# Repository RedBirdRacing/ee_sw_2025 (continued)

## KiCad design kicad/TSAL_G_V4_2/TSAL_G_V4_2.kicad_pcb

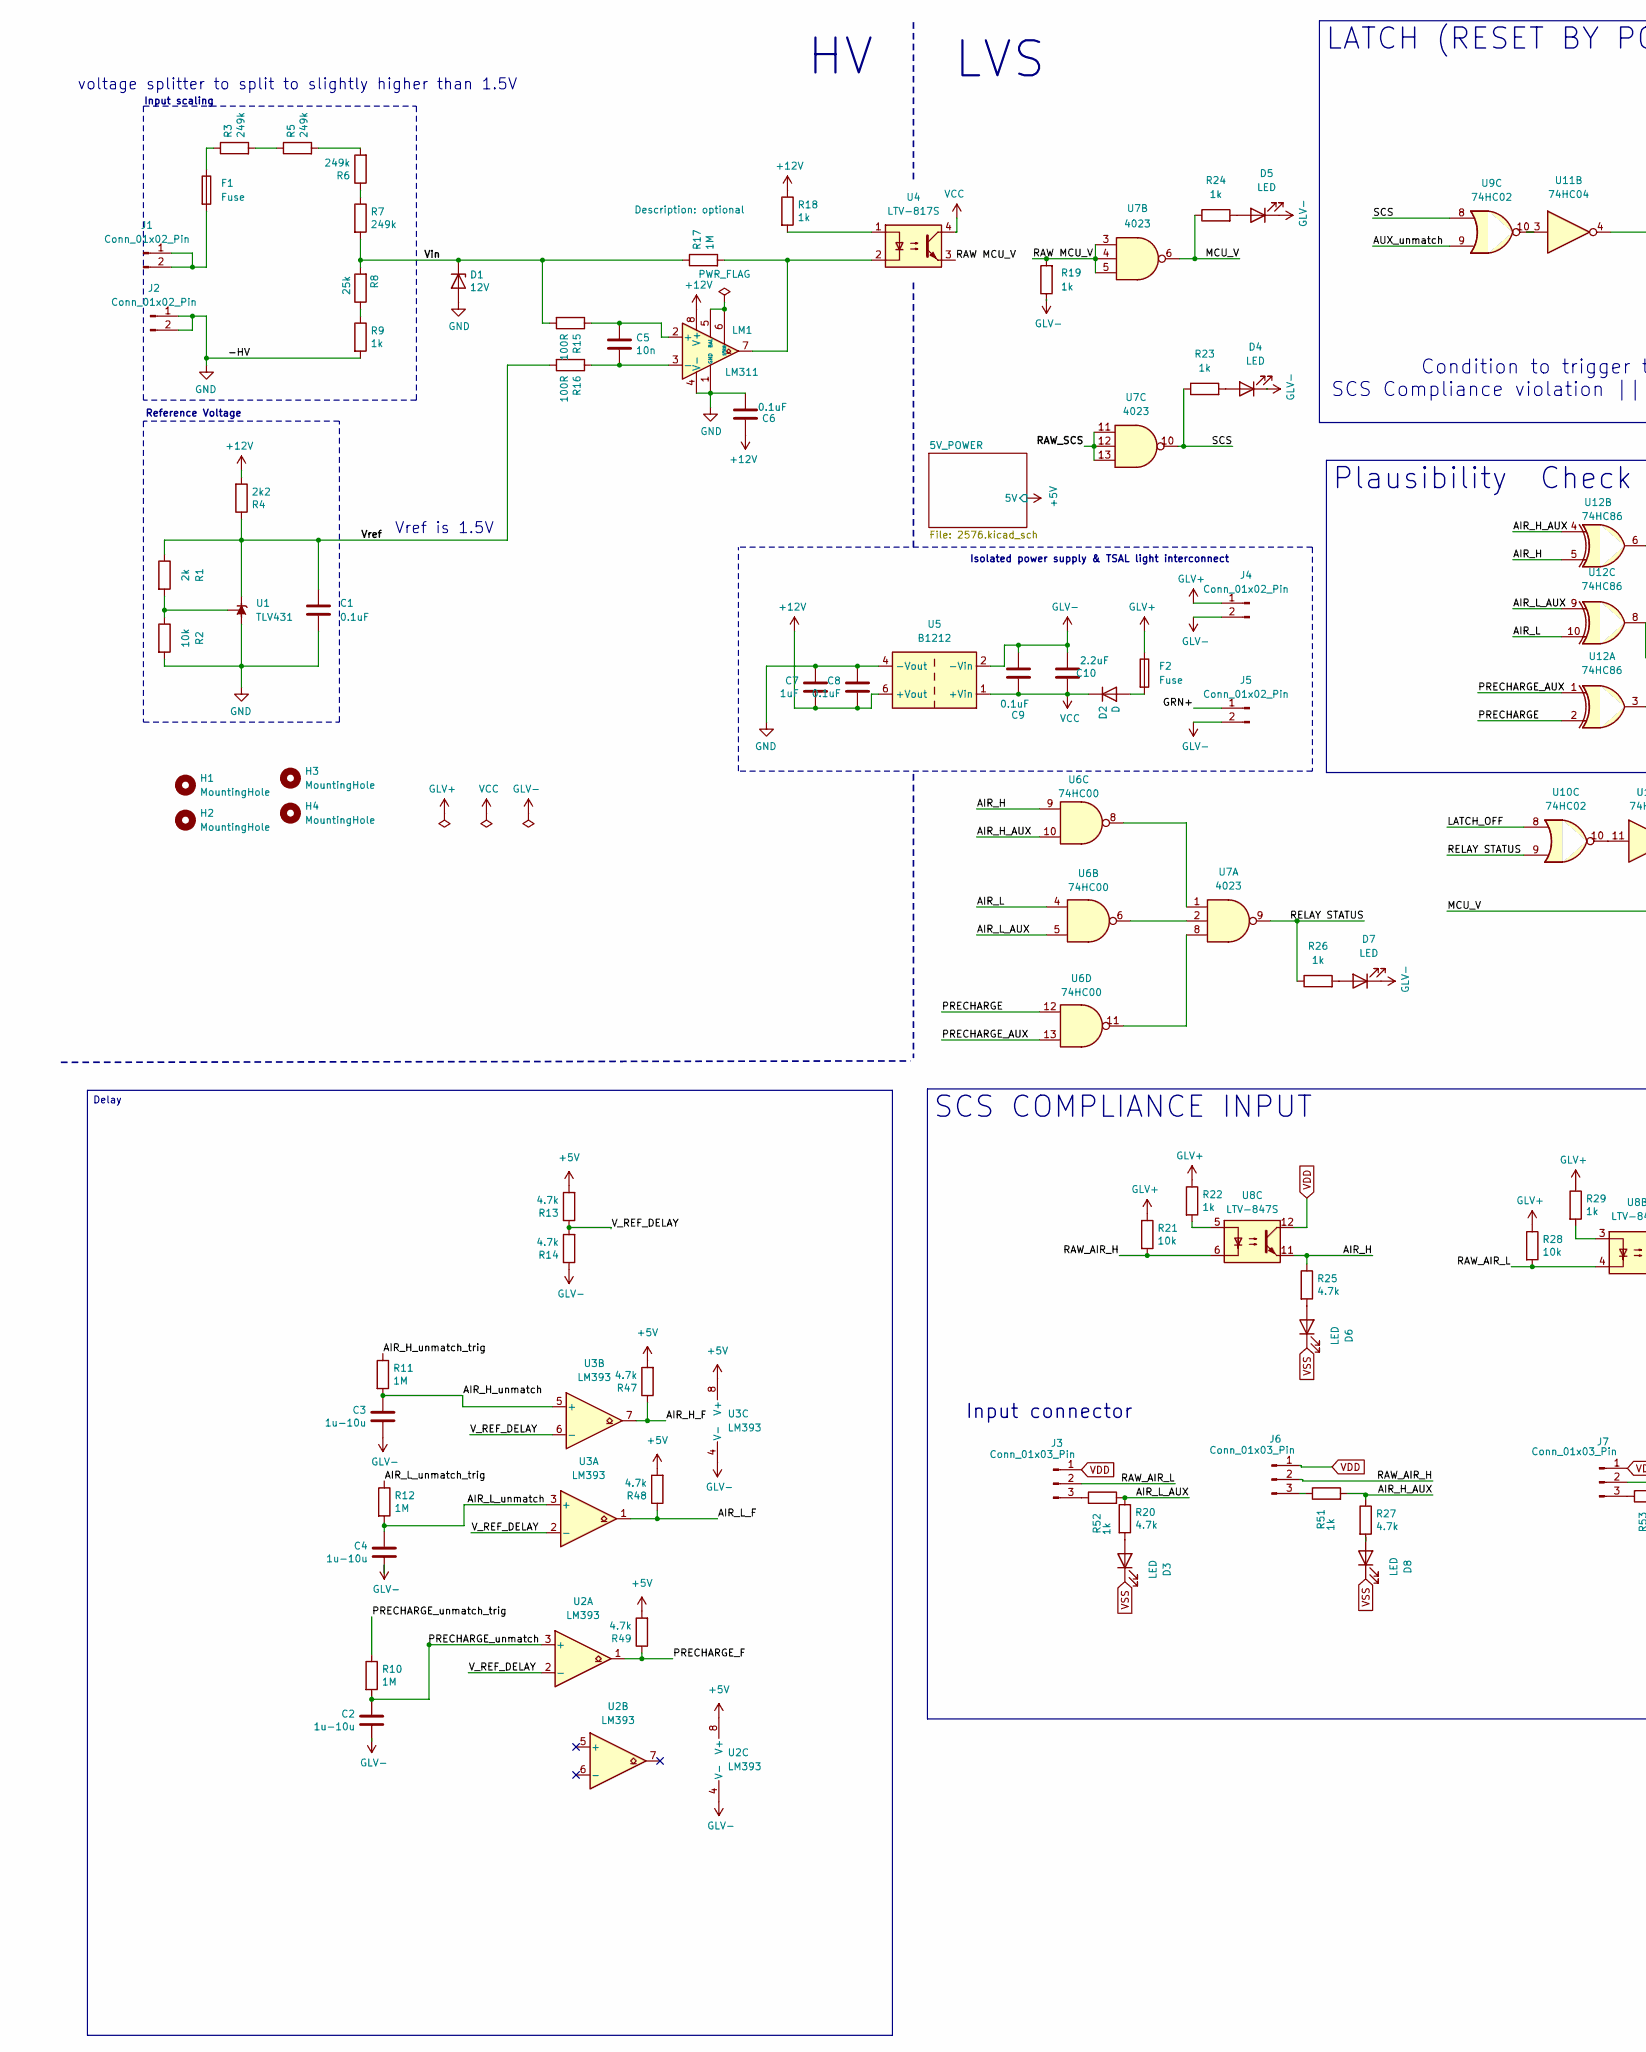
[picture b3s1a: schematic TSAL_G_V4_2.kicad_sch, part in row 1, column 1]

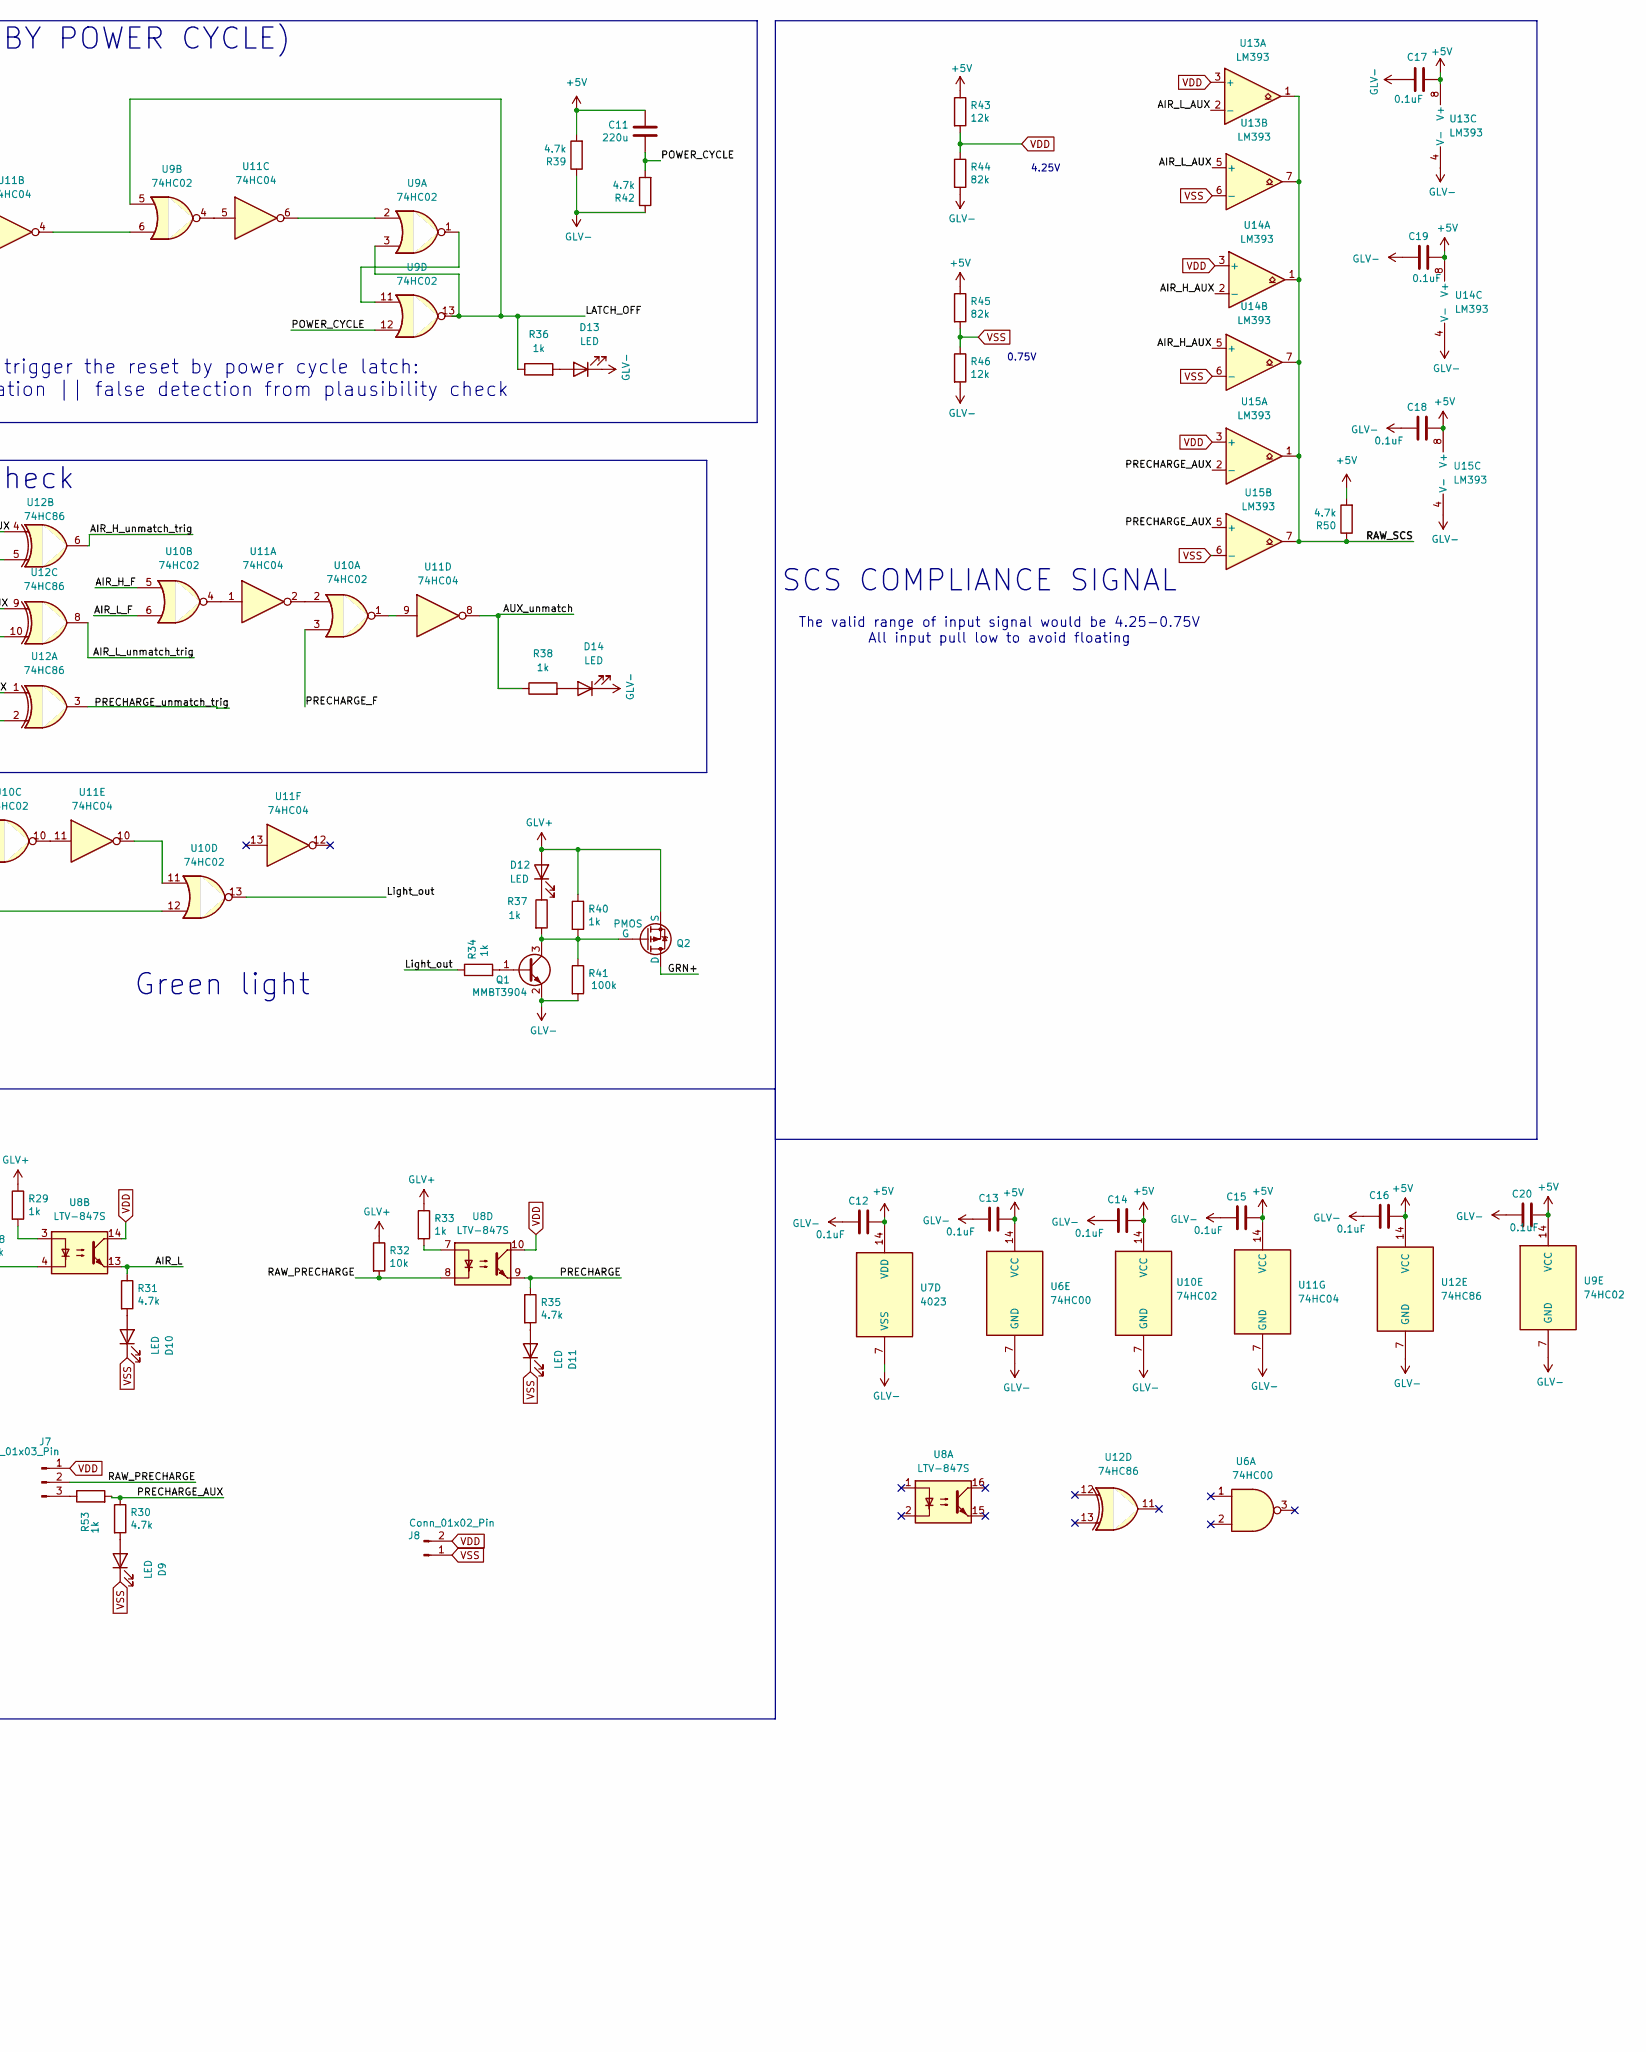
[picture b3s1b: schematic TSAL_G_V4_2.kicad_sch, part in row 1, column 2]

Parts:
C1, C6, C8, C9, C12, C13, C14, C15, C16, C17, C18, C19, C20: 0.1uF; C_0805_2012Metric_Pad1.18x1.45mm_HandSolder_L
C2, C3, C4: 1u-10u; C_0805_2012Metric_Pad1.18x1.45mm_HandSolder_L
C5: 10n; C_0805_2012Metric_Pad1.18x1.45mm_HandSolder_L
C7: 1uF; C_0805_2012Metric_Pad1.18x1.45mm_HandSolder_L
C10: 2.2uF; C_0805_2012Metric_Pad1.18x1.45mm_HandSolder_L
C11: 220u; CP_Radial_D5.0mm_P2.50mm
D1: 12V; D_DO-35_SOD27_P7.62mm_Horizontal
D2: D; D_SMA_Handsoldering
D3, D4, D5, D6, D7, D8, D9, D10, D11, D12, D13, D14: LED; LED_0805_2012Metric_Pad1.45x1.40mm_HandSolder
F1: Fuse; Fuse_Littelfuse-NANO2-885
F2: Fuse; Fuse_1210_3225Metric_Pad1.42x2.65mm_HandSolder
H1, H2, H3, H4: MountingHole; MountingHole_4.3mm_M4
J1, J2, J4, J5, J8: Conn_01x02_Pin; Molex_Micro-Fit_3.0_43650-0215_1x02_P3.00mm_Vertical
J3, J6, J7: Conn_01x03_Pin; Molex_Micro-Fit_3.0_43650-0315_1x03_P3.00mm_Vertical
LM1: LM311; SOIC-8_3.9x4.9mm_P1.27mm_RMC_Handsolder
Q1: MMBT3904; SOT-23
Q2: PMOS; TO-252-2
R1: 2k; R_0805_2012Metric_Pad1.20x1.40mm_HandSolder_L
R2, R21, R28, R32: 10k; R_0805_2012Metric_Pad1.20x1.40mm_HandSolder_L
R3, R5, R6, R7: 249k; R_0805_2012Metric_Pad1.20x1.40mm_HandSolder_L
R4: 2k2; R_0805_2012Metric_Pad1.20x1.40mm_HandSolder_L
R8: 25k; R_0805_2012Metric_Pad1.20x1.40mm_HandSolder_L
R9, R18, R19, R22, R23, R24, R26, R29, R33, R34, R36, R37, R38, R40, R51, R52, R53: 1k; R_0805_2012Metric_Pad1.20x1.40mm_HandSolder_L
R10, R11, R12, R17: 1M; R_0805_2012Metric_Pad1.20x1.40mm_HandSolder_L
R13, R14, R20, R25, R27, R30, R31, R35, R39, R42, R47, R48, R49, R50: 4.7k; R_0805_2012Metric_Pad1.20x1.40mm_HandSolder_L
R15, R16: 100R; R_0805_2012Metric_Pad1.20x1.40mm_HandSolder_L
R41: 100k; R_0805_2012Metric_Pad1.20x1.40mm_HandSolder_L
R43, R46: 12k; R_0805_2012Metric_Pad1.20x1.40mm_HandSolder_L
R44, R45: 82k; R_0805_2012Metric_Pad1.20x1.40mm_HandSolder_L
U1: TLV431; SOT-23
U2, U3, U13, U14, U15: LM393; SOIC-8_3.9x4.9mm_P1.27mm_RMC_Handsolder
U4: LTV-817S; SMDIP-4_W9.53mm
U5: B1212; Converter_DCDC_F1212
U6: 74HC00; SOIC127P600X175-14N
U7: 4023; SOIC127P600X175-14N
U8: LTV-847S; SMDIP-16_W9.53mm
U9, U10: 74HC02; SOIC127P600X175-14N
U11: 74HC04; SOIC127P600X175-14N
U12: 74HC86; SOIC127P600X175-14N

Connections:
+5V: C11.1, C12.2, C13.2, C14.2, C15.2, C16.2, C17.2, C18.2, C19.2, C20.2, R13.2, R39.2, R43.1, R45.1, R47.2, R48.2, R49.2, R50.2, U2.8 (V+), U3.8 (V+), U6.14 (VCC), U7.14 (VDD), U9.14 (VCC), U10.14 (VCC), U11.14 (VCC), U12.14 (VCC), U13.8 (V+), U14.8 (V+), U15.8 (V+); also elsewhere on the board
+12V: C6.1, C7.2, C8.2, LM1.8 (V+), R4.2, R18.1, U5.6 (+Vout)
/AIR_H: R25.1, U6.9, U8.11, U12.5
/AIR_H_AUX: R27.1, R51.2, U6.10, U12.4, U14.2 (-), U14.5 (+)
/AIR_H_F: R47.1, U3.7, U10.5
/AIR_H_unmatch: C3.1, R11.2, U3.5 (+)
/AIR_H_unmatch_trig: R11.1, U12.6
/AIR_L: R31.1, U6.4, U8.13, U12.10
/AIR_L_AUX: R20.1, R52.2, U6.5, U12.9, U13.2 (-), U13.5 (+)
/AIR_L_F: R48.1, U3.1, U10.6
/AIR_L_unmatch: C4.1, R12.2, U3.3 (+)
/AIR_L_unmatch_trig: R12.1, U12.8
/AUX_unmatch: R38.1, U9.9, U11.8
/GRN+: J5.1, Q2.1 (D)
/LATCH_OFF: R36.1, U9.3, U9.5, U9.13, U10.8
/Light_out: R34.1, U10.13
/MCU_V: R24.1, U7.6, U10.12
/POWER_CYCLE: C11.2, R42.2, U9.12
/PRECHARGE: R35.1, U6.12, U8.9, U12.2
/PRECHARGE_AUX: R30.1, R53.2, U6.13, U12.1, U15.2 (-), U15.5 (+)
/PRECHARGE_F: R49.1, U2.1, U10.3
/PRECHARGE_unmatch: C2.1, R10.2, U2.3 (+)
/PRECHARGE_unmatch_trig: R10.1, U12.3
/RAW MCU_V: R19.2, U4.3, U7.3, U7.4, U7.5
/RAW_AIR_H: J6.2, R21.2, U8.6
/RAW_AIR_L: J3.2, R28.2, U8.4
/RAW_PRECHARGE: J7.2, R32.2, U8.8
/RAW_SCS: R50.1, U7.11, U7.12, U7.13, U13.1, U13.7, U14.1, U14.7, U15.1, U15.7
/RELAY STATUS: R26.1, U7.9, U10.9
/SCS: R23.1, U7.10, U9.8
/V_REF_DELAY: R13.1, R14.2, U2.2 (-), U3.2 (-), U3.6 (-)
/Vin: D1.1 (K), R7.2, R8.2, R15.2, R17.1
/Vref: C1.1, R1.1, R4.1, R16.2, U1.2 (K)
GLV+: D12.2 (A), F2.1, J4.1, Q2.3 (S), R21.1, R22.1, R28.1, R29.1, R32.1, R33.1, R40.1
GLV-: C2.2, C3.2, C4.2, C9.1, C10.1, C12.1, C13.1, C14.1, C15.1, C16.1, C17.1, C18.1, C19.1, C20.1, D4.1 (K), D5.1 (K), D7.1 (K), D13.1 (K), D14.1 (K), J4.2, J5.2, Q1.2 (E), R14.1, R19.1, R39.1, R41.2, R42.1, R44.2, R46.2, U2.4 (V-), U3.4 (V-), U5.2 (-Vin), U6.7 (GND), U7.7 (VSS), U9.7 (GND), U10.7 (GND), U11.7 (GND), U12.7 (GND), U13.4 (V-), U14.4 (V-), U15.4 (V-); also elsewhere on the board
GND: C1.2, C6.2, C7.1, C8.1, D1.2 (A), J2.1, J2.2, LM1.1 (GND), LM1.4 (V-), R2.2, R9.2, U1.3 (A), U5.4 (-Vout)
unnamed: D2.2 (A), F2.2
unnamed: D3.2 (A), R20.2
unnamed: D4.2 (A), R23.2
unnamed: D5.2 (A), R24.2
unnamed: D6.2 (A), R25.2
unnamed: D7.2 (A), R26.2
unnamed: D8.2 (A), R27.2
unnamed: D9.2 (A), R30.2
unnamed: D10.2 (A), R31.2
unnamed: D11.2 (A), R35.2
unnamed: D12.1 (K), R37.1
unnamed: D13.2 (A), R36.2
unnamed: D14.2 (A), R38.2
unnamed: F1.1, R3.1
unnamed: F1.2, J1.1, J1.2
unnamed: J3.3, R52.1
unnamed: J6.3, R51.1
unnamed: J7.3, R53.1
unnamed: C5.1, LM1.2 (+), R15.1
unnamed: C5.2, LM1.3 (-), R16.1
unnamed: LM1.5 (BAL), LM1.6 (STRB)
unnamed: LM1.7, R17.2, U4.2
unnamed: Q1.1 (B), R34.2
unnamed: Q1.3 (C), Q2.2 (G), R37.2, R40.2, R41.1
unnamed: R3.2, R5.1
unnamed: R5.2, R6.2
unnamed: R6.1, R7.1
unnamed: R8.1, R9.1
unnamed: R18.2, U4.1
unnamed: R22.2, U8.5
unnamed: R29.2, U8.3
unnamed: R33.2, U8.7
unnamed: R1.2, R2.1, U1.1 (REF)
unnamed: U6.6, U7.2
unnamed: U6.8, U7.1
unnamed: U6.11, U7.8
unnamed: U9.1, U9.11
unnamed: U10.1, U11.9
unnamed: U10.2, U11.2
unnamed: U10.4, U11.1
unnamed: U10.10, U11.11
unnamed: U10.11, U11.10
unnamed: U9.10, U11.3
unnamed: U9.6, U11.4
unnamed: U9.4, U11.5
unnamed: U9.2, U11.6
VCC: C9.2, C10.2, D2.1 (K), U4.4, U5.1 (+Vin); also elsewhere on the board
VDD: J3.1, J6.1, J7.1, J8.2, R43.2, R44.1, U8.10, U8.12, U8.14, U13.3 (+), U14.3 (+), U15.3 (+)
VSS: D3.1 (K), D6.1 (K), D8.1 (K), D9.1 (K), D10.1 (K), D11.1 (K), J8.1, R45.2, R46.1, U13.6 (-), U14.6 (-), U15.6 (-)

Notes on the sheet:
0.75V
The valid range of input signal would be 4.25-0.75V All input pull low to avoid floating
LVS
Condition to trigger the reset by power cycle latch: SCS Compliance violation || false detection from plausibility check
Reference Voltage
voltage splitter to split to slightly higher than 1.5V
Vref is 1.5V
Green light
Isolated power supply & TSAL light interconnect
Input scaling
4.25V
Input connector
Plausibility Check
SCS COMPLIANCE SIGNAL
Delay
LATCH (RESET BY POWER CYCLE)
SCS COMPLIANCE INPUT

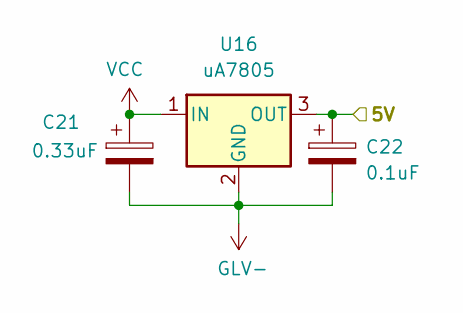
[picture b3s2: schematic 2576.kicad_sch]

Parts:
C21: 0.33uF; CP_Radial_D5.0mm_P2.50mm
C22: 0.1uF; CP_Radial_D5.0mm_P2.50mm
U16: uA7805; TO-252-2

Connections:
+5V: C22.1, U16.3 (OUT); also elsewhere on the board
GLV-: C21.2, C22.2, U16.2 (GND); also elsewhere on the board
VCC: C21.1, U16.1 (IN); also elsewhere on the board

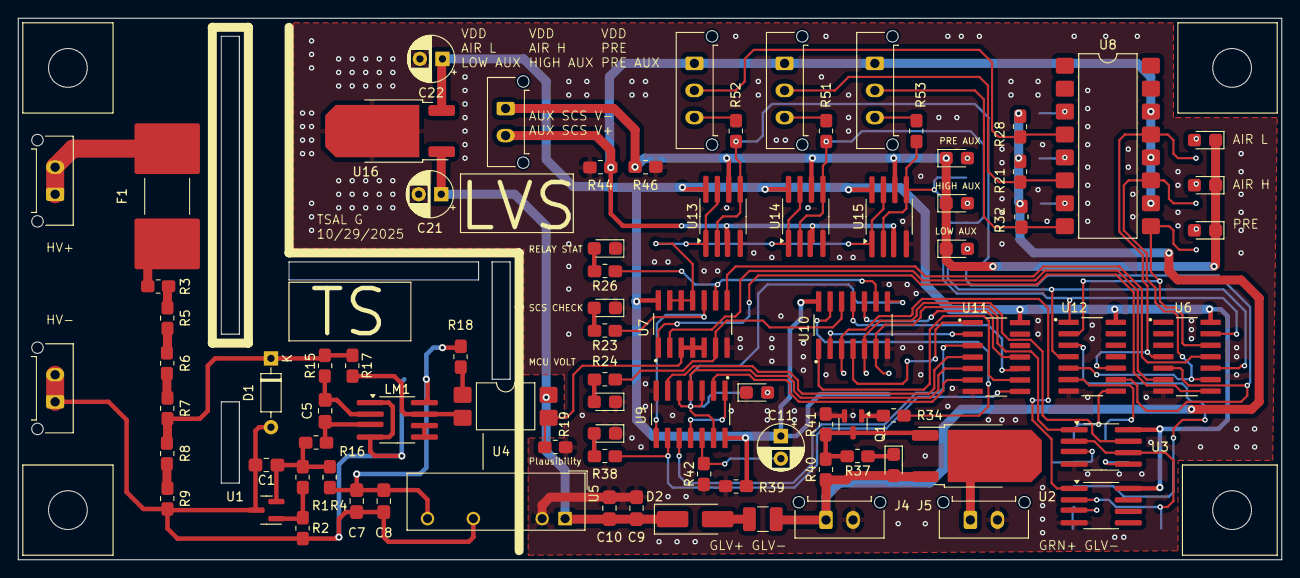
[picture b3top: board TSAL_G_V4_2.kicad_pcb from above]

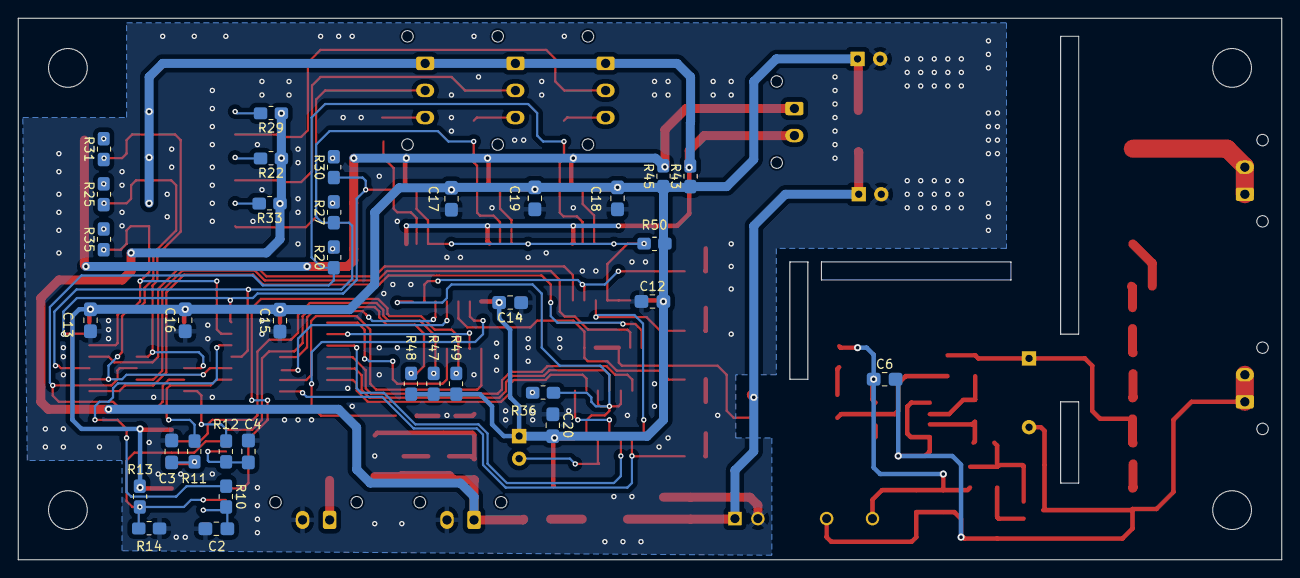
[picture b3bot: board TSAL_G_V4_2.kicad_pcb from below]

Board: 2 copper layers, 140.0 x 60.0 mm, 122 parts (34 on the bottom side), 85 nets.

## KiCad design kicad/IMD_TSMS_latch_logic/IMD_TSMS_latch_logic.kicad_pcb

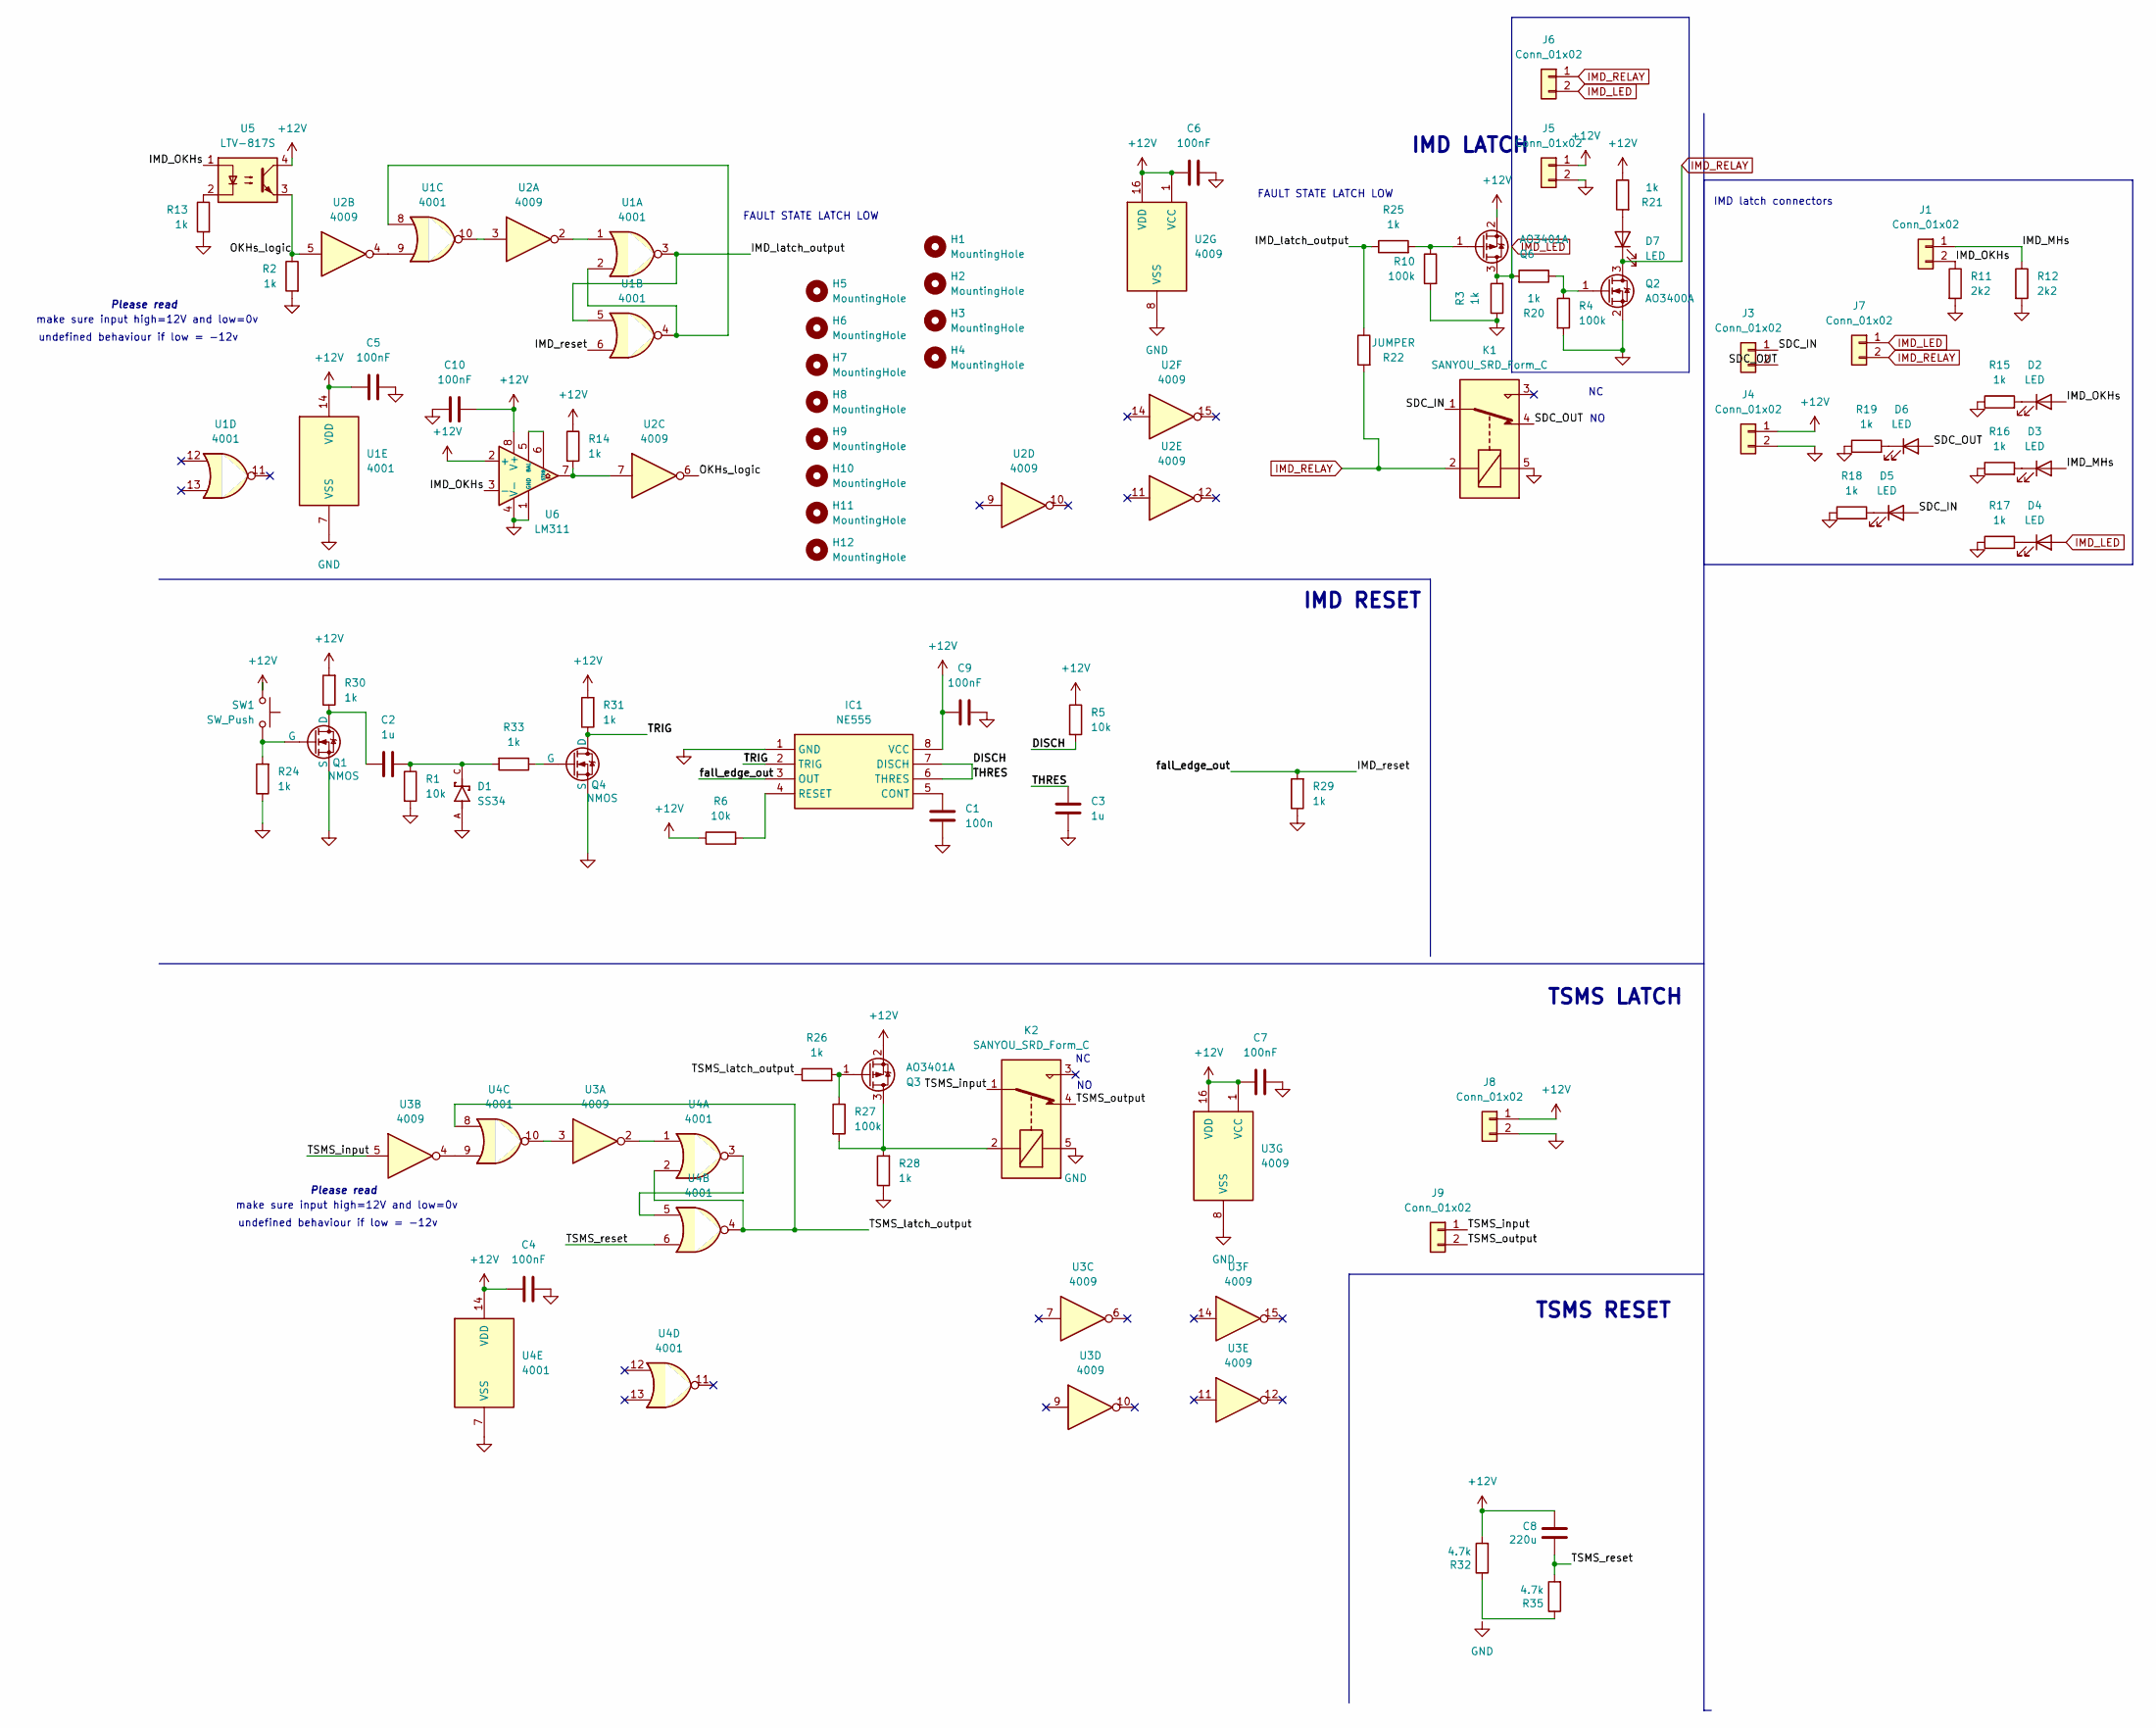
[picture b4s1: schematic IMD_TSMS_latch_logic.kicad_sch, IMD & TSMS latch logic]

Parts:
C1: 100n; C_0805_2012Metric_Pad1.18x1.45mm_HandSolder
C2, C3: 1u; C_0805_2012Metric_Pad1.18x1.45mm_HandSolder
C4, C5, C6, C7, C9, C10: 100nF; C_0805_2012Metric_Pad1.18x1.45mm_HandSolder
C8: 220u; CP_Radial_D6.3mm_P2.50mm
D1: SS34; SS34 (1N5822); PARTREV 31 Aug 2016
D2, D3, D4, D5, D6, D7: LED; LED_0805_2012Metric_Pad1.15x1.40mm_HandSolder
H1, H2, H3, H4, H5, H6, H7, H8, H9, H10, H11, H12: MountingHole; MountingHole_4.3mm_M4
IC1: NE555; SOIC-8_3.9x4.9mm_P1.27mm; Manufacturer_Part_Number NE555; Mouser Part Number N/A
J1, J3, J4, J5, J6, J7, J8, J9: Conn_01x02; Molex_Micro-Fit_3.0_43650-0215_1x02_P3.00mm_Vertical
K1, K2: SANYOU_SRD_Form_C; Relay_SPDT_SANYOU_SRD_Series_Form_C
Q1, Q4: NMOS; SOT-23
Q2: AO3400A; SOT-23
Q3, Q6: AO3401A; SOT-23
R1, R5, R6: 10k; R_0805_2012Metric_Pad1.20x1.40mm_HandSolder
R2, R3, R13, R14, R15, R16, R17, R18, R19, R20, R21, R24, R25, R26, R28, R29, R30, R31, R33: 1k; R_0805_2012Metric_Pad1.20x1.40mm_HandSolder
R4, R10, R27: 100k; R_0805_2012Metric_Pad1.20x1.40mm_HandSolder
R11, R12: 2k2; R_0805_2012Metric_Pad1.20x1.40mm_HandSolder
R22: JUMPER; R_0805_2012Metric_Pad1.20x1.40mm_HandSolder
R32, R35: 4.7k; R_0805_2012Metric_Pad1.20x1.40mm_HandSolder
SW1: SW_Push; Molex_Micro-Fit_3.0_43650-0215_1x02_P3.00mm_Vertical
U1, U4: 4001; SOIC127P600X175-14N
U2, U3: 4009; SOIC-16_3.9x9.9mm_P1.27mm
U5: LTV-817S; SMDIP-4_W9.53mm
U6: LM311; SOIC-8_3.9x4.9mm_P1.27mm

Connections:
+12V: C4.1, C5.1, C6.1, C7.1, C8.1, C9.1, C10.1, IC1.8 (VCC), J4.1, J5.1, J8.1, Q3.2 (S), Q6.2 (S), R5.1, R6.1, R14.1, R21.1, R30.2, R31.2, R32.2, SW1.2, U1.14 (VDD), U2.1 (VCC), U2.16 (VDD), U3.1 (VCC), U3.16 (VDD), U4.14 (VDD), U5.4, U6.2 (+), U6.8 (V+)
/DISCH: C3.1, IC1.6 (THRES), IC1.7 (DISCH), R5.2
/IMD_MHs: D3.2 (A), J1.1, R12.1
/IMD_OKHs: D2.2 (A), J1.2, R11.1, U5.1, U6.3 (-)
/IMD_latch_output: R22.1, R25.1, U1.3, U1.5
/IMD_reset: IC1.3 (OUT), R29.2, U1.6
/OKHs_logic: R2.1, U2.5, U2.6, U5.3
/SDC_IN: D5.2 (A), J3.1, K1.1
/SDC_OUT: D6.2 (A), J3.2, K1.4
/TRIG: IC1.2 (TRIG), Q4.1 (D), R31.1
/TSMS_input: J9.1, K2.1, U3.5
/TSMS_latch_output: R26.1, U4.2, U4.4, U4.8
/TSMS_output: J9.2, K2.4
/TSMS_reset: C8.2, R35.2, U4.6
GND: C1.2, C3.2, C4.2, C5.2, C6.2, C7.2, C9.2, C10.2, D1.A, IC1.1 (GND), J4.2, J5.2, J8.2, K1.5, K2.5, Q1.3 (S), Q2.2 (S), Q4.3 (S), R1.2, R2.2, R3.1, R4.2, R10.2, R11.2, R12.2, R13.2, R15.1, R16.1, R17.1, R18.1, R19.1, R24.1, R28.1, R29.1, U1.7 (VSS), U2.8 (VSS), U3.8 (VSS), U4.7 (VSS), U6.1 (GND), U6.4 (V-)
IMD_LED: D4.2 (A), J6.2, J7.1, Q6.3 (D), R3.2, R20.2
IMD_RELAY: D7.1 (K), J6.1, J7.2, K1.2, Q2.3 (D), R22.2
unnamed: C2.2, D1.C, R1.1, R33.2
unnamed: D2.1 (K), R15.2
unnamed: D3.1 (K), R16.2
unnamed: D4.1 (K), R17.2
unnamed: D5.1 (K), R18.2
unnamed: D6.1 (K), R19.2
unnamed: D7.2 (A), R21.2
unnamed: C1.1, IC1.5 (CONT)
unnamed: IC1.4 (RESET), R6.2
unnamed: C2.1, Q1.1 (D), R30.1
unnamed: Q1.2 (G), R24.2, SW1.1
unnamed: Q2.1 (G), R4.1, R20.1
unnamed: K2.2, Q3.3 (D), R27.2, R28.2
unnamed: Q3.1 (G), R26.2, R27.1
unnamed: Q4.2 (G), R33.1
unnamed: Q6.1 (G), R10.1, R25.2
unnamed: R13.1, U5.2
unnamed: R14.2, U2.7, U6.7
unnamed: R32.1, R35.1
unnamed: U1.1, U2.2
unnamed: U1.2, U1.4, U1.8
unnamed: U1.9, U2.4
unnamed: U1.10, U2.3
unnamed: U3.2, U4.1
unnamed: U3.3, U4.10
unnamed: U3.4, U4.9
unnamed: U4.3, U4.5
unnamed: U6.5 (BAL), U6.6 (STRB)

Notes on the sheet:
FAULT STATE LATCH LOW
make sure input high=12V and low=0v
IMD latch connectors
undefined behaviour if low = -12v
Please read
TSMS LATCH
IMD RESET
TSMS RESET
IMD LATCH

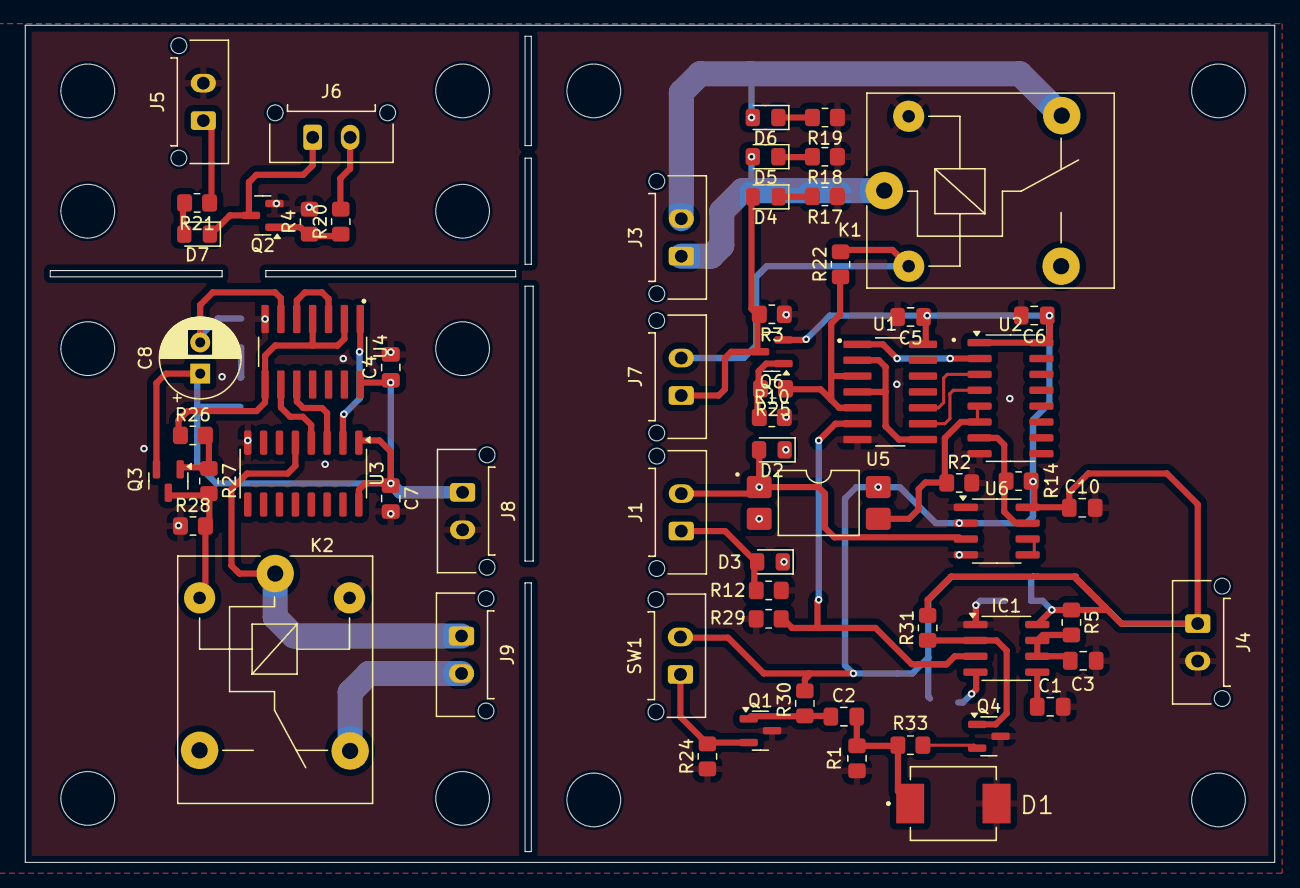
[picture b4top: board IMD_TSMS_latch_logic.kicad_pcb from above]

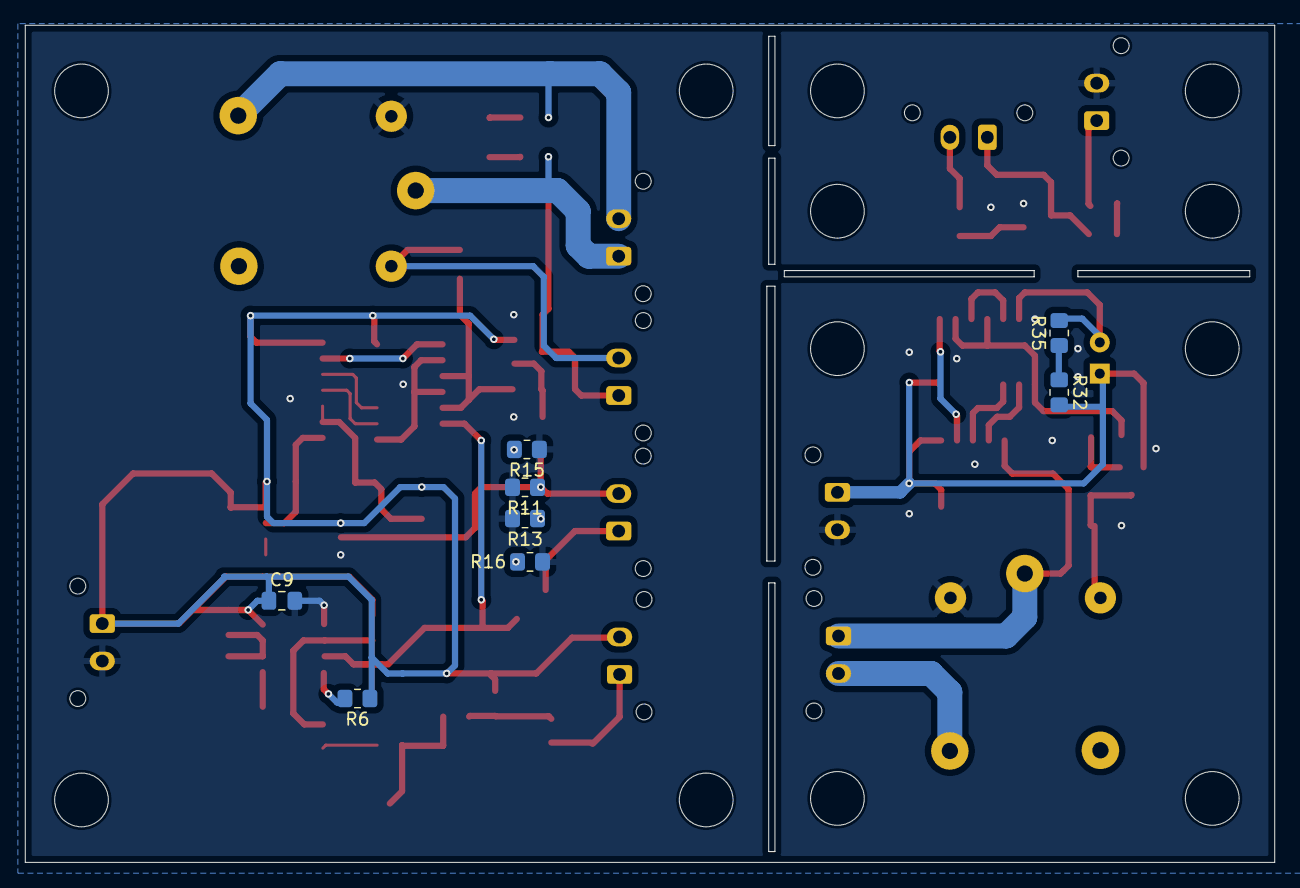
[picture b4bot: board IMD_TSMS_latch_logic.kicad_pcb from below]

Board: 2 copper layers, 100.0 x 67.0 mm, 82 parts (8 on the bottom side), 45 nets.
